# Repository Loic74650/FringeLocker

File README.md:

# FringeLocker
## Intro
 FringeLocker, as its name indicates, is an electronic system designed to lock interference fringes of an optical interferometer or a holography recording setup.
 The purpose of locking an interferometer is usually to stabilize unstable interference fringes due to mechanical vibrations or thermal drifts.<br />
 Demo video: https://youtu.be/0IrlpE1sPkQ
 
  <br />
  <br />
  <br />
  <br /><br />
 
## Working principle
Two photodiodes sample the interference fringes and detect any movement of those. 
A low noise amplifier and feedback loop drive a mirror which is placed on a piezo transducer in order to move one arm of the interferometer and compensate for the detected fringe movements

## Setup
This version of FringeLocker is powered by two MN21/A23 12V batteries. Alternatively connector J3 on the board can be used to power the board with an external supply of
your choice (remove the batteries first!). The board accepts supply voltages up to +/-18Volts and so currently I am using two 9V batteries in series for each voltage ramp in order to increase lifetime on battery.
The photodiodes need to be masked of, leaving just one slit 0.5mm wide per photodiode. See image in the photos folder.<br />
Slider switch SW2 switched ON/OFF the board.  
There are three adjustments to be performed on the board. 

1- Servo Gain
RV1 10 turns potentiometer adjusts the servo gain. Start by adjusting it to minimum

2- Output bias
RV2 10 turns potentiometer adjusts the level of bias voltage to the piezo transducer. Since positive or negative voltages can be applied to the transducer it is necessary to apply
a bias to it. Use a voltmeter to measure the bias voltage between ground (the pcb mounting holes in each corner are grounded) and Test Point 2 (TP2 or TP Bias) and adjust it to 18 volts or so.

3- PresScaler switch
SW1 is a rotary switch which selects a preamplification of the photodiodes signal with various gains. Start by adjusting it to minimum

## Servo loop adjustment
Place the photodiodes within interference fringes of the interferometer. Adjust the interference fringes spacing so that their spacing is approximately 15mm (twice the spacing between the photodiodes). 
Power the board and start with the lowest gain on the PreScaler switch SW1 and move to larger gains incrementally until the feedback loop starts oscillating.
Revert to the previous gain setting in order to stop the oscillation. You can then fine adjust the loop gain RV1 by increasing it slowly until the loop starts oscillating, then reverting a bit to stop the oscillation.

## Bugs
An unpolarized 100nF capacitor needs to be manually added in parallel with R2 in order to create an active low pass filter and prevent the feedback loop from oscillating

## Credits
Thanks to Phil Hobbs for his help on the schematic design

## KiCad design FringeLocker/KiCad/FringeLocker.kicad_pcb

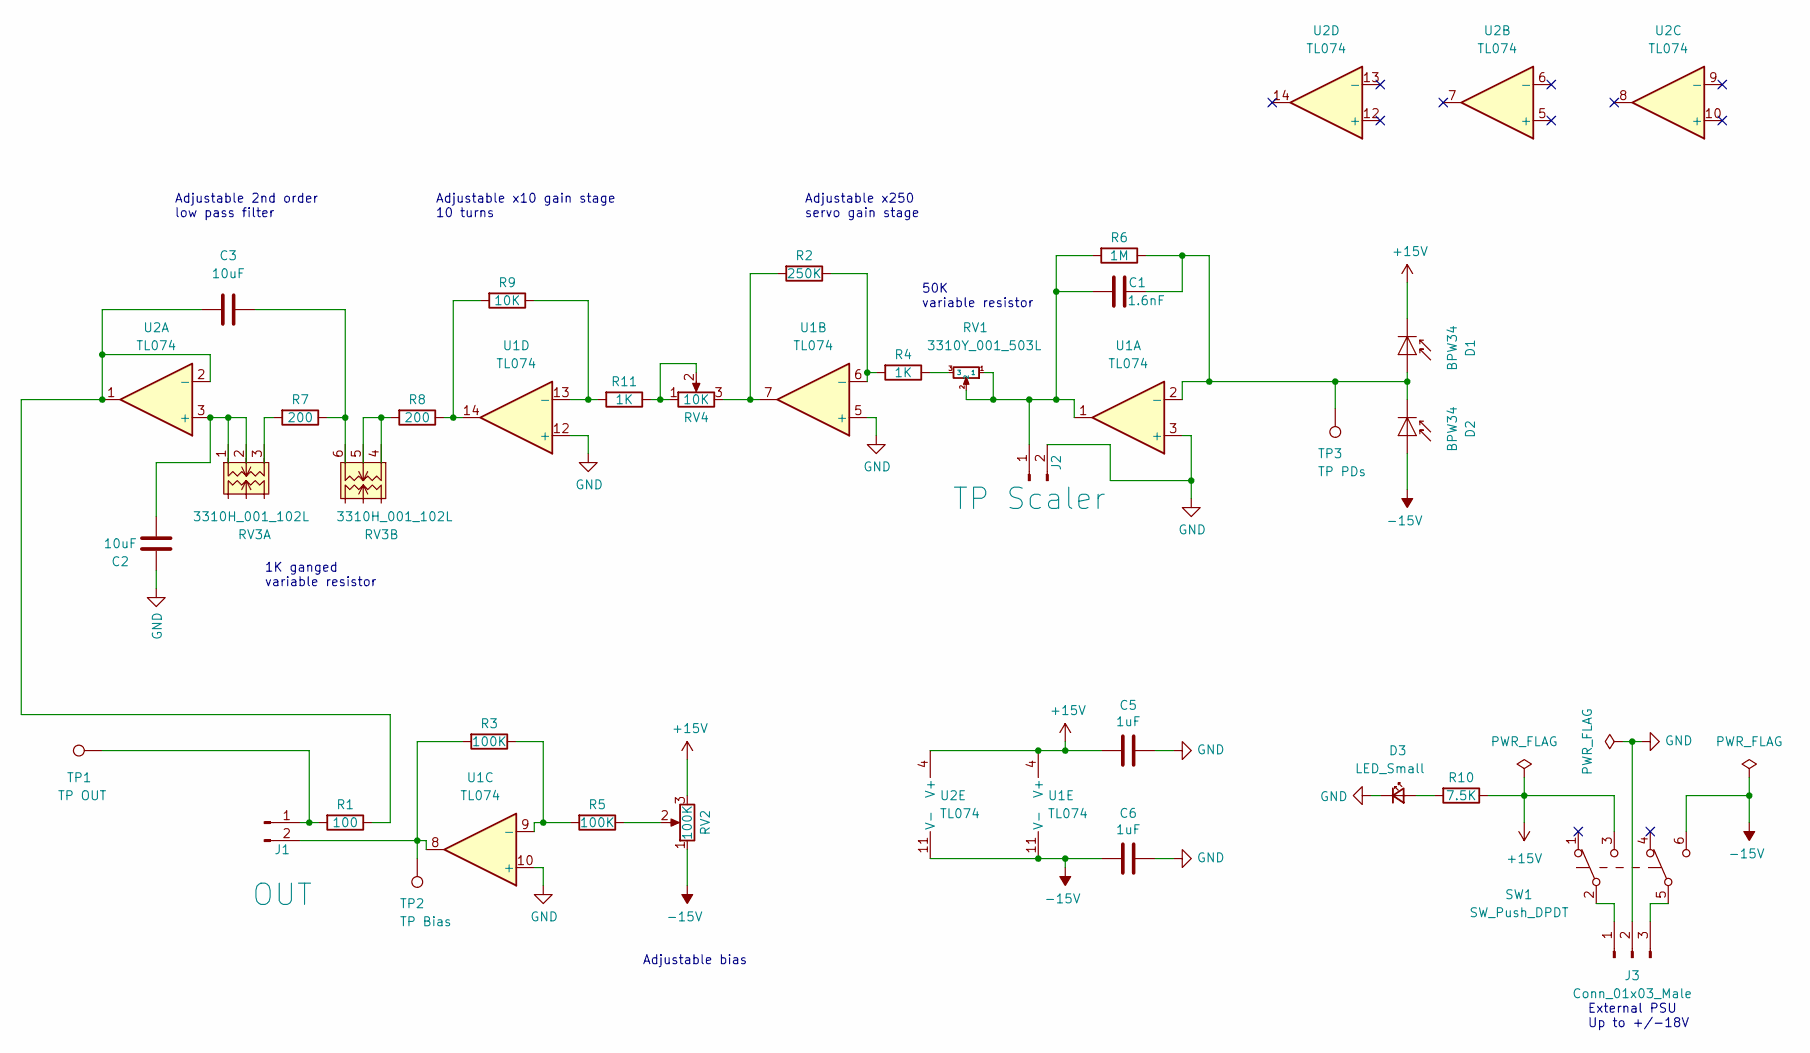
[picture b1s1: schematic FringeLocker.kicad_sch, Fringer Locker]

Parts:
C1: 1.6nF; C_0603_1608Metric_Pad1.08x0.95mm_HandSolder
C2, C3: 10uF; C_1210_3225Metric_Pad1.33x2.70mm_HandSolder
C5, C6: 1uF; C_0603_1608Metric_Pad1.08x0.95mm_HandSolder
D1, D2: BPW34; Osram_DIL2_4.3x4.65mm_P5.08mm
D3: LED_Small; LED_0805_2012Metric_Pad1.15x1.40mm_HandSolder
J1: OUT; PinHeader_1x02_P2.54mm_Vertical
J2: TP Scaler; PinHeader_1x02_P2.54mm_Vertical
J3: Conn_01x03_Male; PinHeader_1x03_P2.54mm_Vertical
R1: 100; R_0805_2012Metric_Pad1.20x1.40mm_HandSolder
R2: 250K; R_0805_2012Metric_Pad1.20x1.40mm_HandSolder
R3, R5: 100K; R_0805_2012Metric_Pad1.20x1.40mm_HandSolder
R4, R11: 1K; R_0805_2012Metric_Pad1.20x1.40mm_HandSolder
R6: 1M; R_0805_2012Metric_Pad1.20x1.40mm_HandSolder
R7, R8: 200; R_0805_2012Metric_Pad1.20x1.40mm_HandSolder
R9: 10K; R_0805_2012Metric_Pad1.20x1.40mm_HandSolder
R10: 7.5K; R_0805_2012Metric_Pad1.20x1.40mm_HandSolder
RV1: 3310Y_001_503L; Bourns3310Y
RV2: 100K; Potentiometer_Bourns_3266W_Vertical
RV3: 3310H_001_102L; Bourns3310H
RV4: 10K; Potentiometer_Bourns_3266W_Vertical
SW1: SW_Push_DPDT; SlideSwitchASE_DPDT
TP1: TP OUT; TestPoint_THTPad_D1.0mm_Drill0.5mm
TP2: TP Bias; TestPoint_THTPad_D1.0mm_Drill0.5mm
TP3: TP PDs; TestPoint_THTPad_D1.0mm_Drill0.5mm
U1, U2: TL074; SO-14_5.3x10.2mm_P1.27mm

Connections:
+15V: C5.1, D1.1 (K), R10.1, RV2.3, SW1.3 (C), U1.4 (V+), U2.4 (V+)
-15V: C6.1, D2.2 (A), RV2.1, SW1.6 (C), U1.11 (V-), U2.11 (V-)
GND: C2.2, C5.2, C6.2, D3.1 (K), J2.2, J3.2, U1.3 (+), U1.5 (+), U1.10 (+), U1.12 (+); also elsewhere on the board
unnamed: C1.1, J2.1, R6.2, RV1.1, RV1.2, U1.1
unnamed: C1.2, D1.2 (A), D2.1 (K), R6.1, TP3.1, U1.2 (-)
unnamed: C2.1, RV3.1 (A), RV3.2 (B), U2.3 (+)
unnamed: C3.1, R7.1, RV3.6 (F)
unnamed: C3.2, R1.1, U2.1, U2.2 (-)
unnamed: D3.2 (A), R10.2
unnamed: J1.1, R1.2, TP1.1
unnamed: J1.2, R3.2, TP2.1, U1.8
unnamed: J3.1, SW1.2 (B)
unnamed: J3.3, SW1.5 (B)
unnamed: R2.1, R4.2, U1.6 (-)
unnamed: R2.2, RV4.3, U1.7
unnamed: R3.1, R5.2, U1.9 (-)
unnamed: R4.1, RV1.3
unnamed: R5.1, RV2.2
unnamed: R7.2, RV3.3 (C)
unnamed: R8.1, R9.2, U1.14
unnamed: R8.2, RV3.4 (D), RV3.5 (E)
unnamed: R11.1, RV4.1, RV4.2
unnamed: R9.1, R11.2, U1.13 (-)

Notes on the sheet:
External PSU Up to +/-18V
Adjustable x10 gain stage 10 turns
Adjustable x250 servo gain stage
1K ganged variable resistor
Adjustable 2nd order low pass filter
50K variable resistor
Adjustable bias

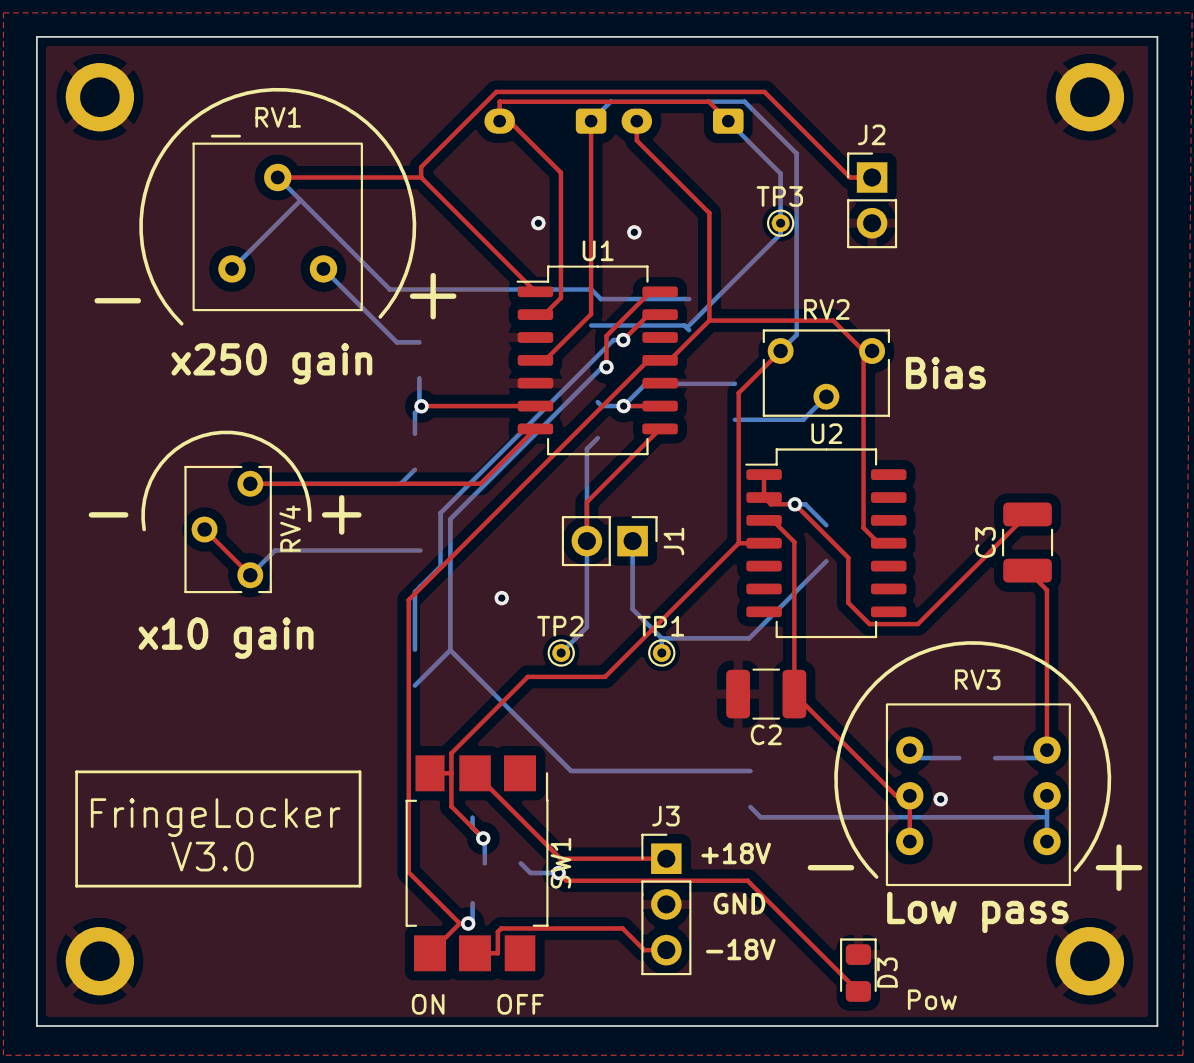
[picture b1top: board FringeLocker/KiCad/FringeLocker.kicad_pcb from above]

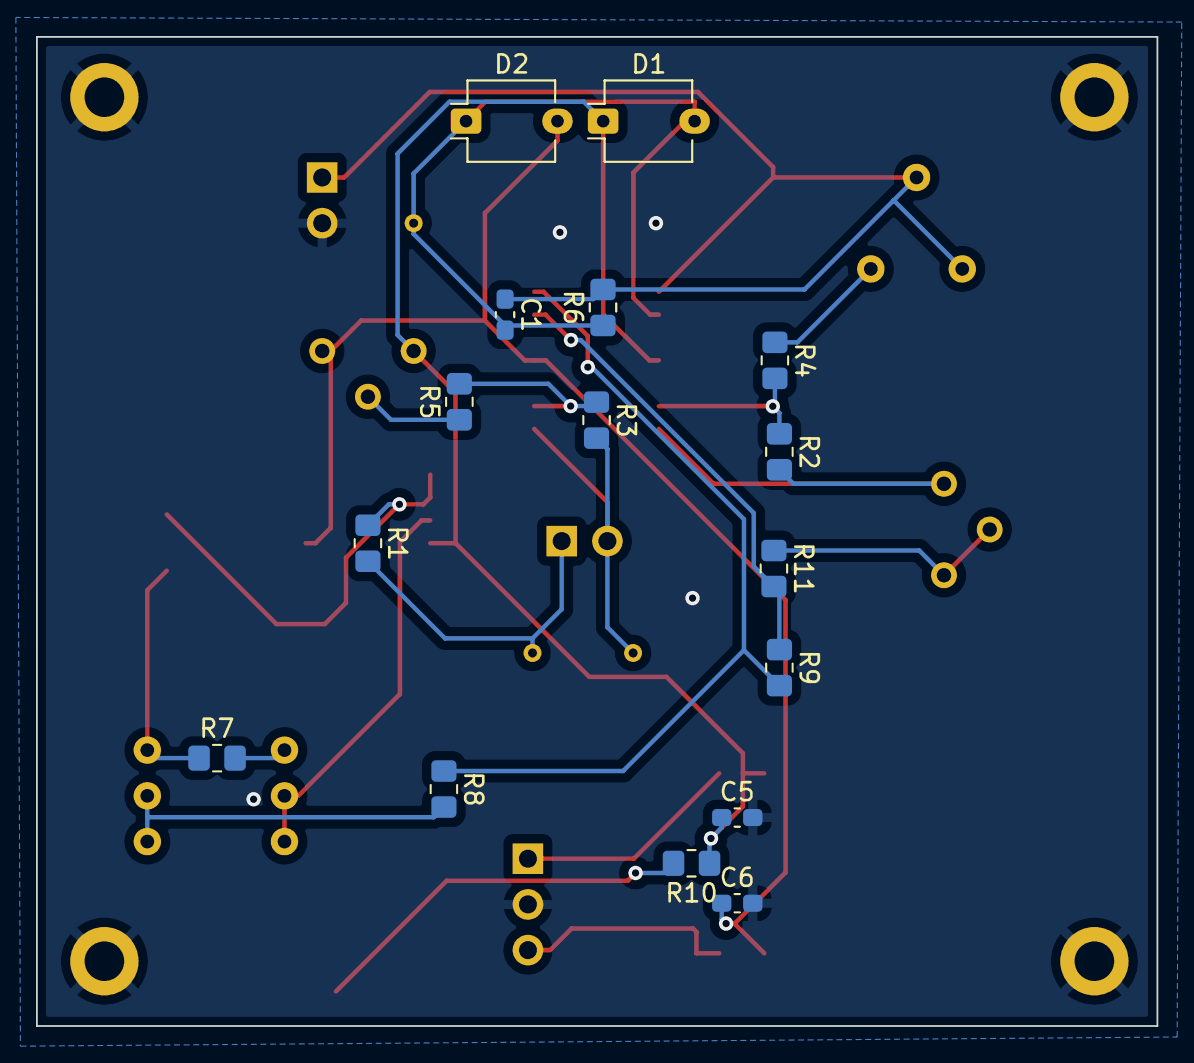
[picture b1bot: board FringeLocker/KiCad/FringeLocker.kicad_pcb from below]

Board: 2 copper layers, 62.2 x 54.9 mm, 36 parts (16 on the bottom side), 23 nets.

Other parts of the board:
REF1, REF2, REF3, REF4: MountingHole_2.2mm_M2_DIN965_Pad

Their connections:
GND: REF1.1, REF2.1, REF3.1, REF4.1; also elsewhere on the board

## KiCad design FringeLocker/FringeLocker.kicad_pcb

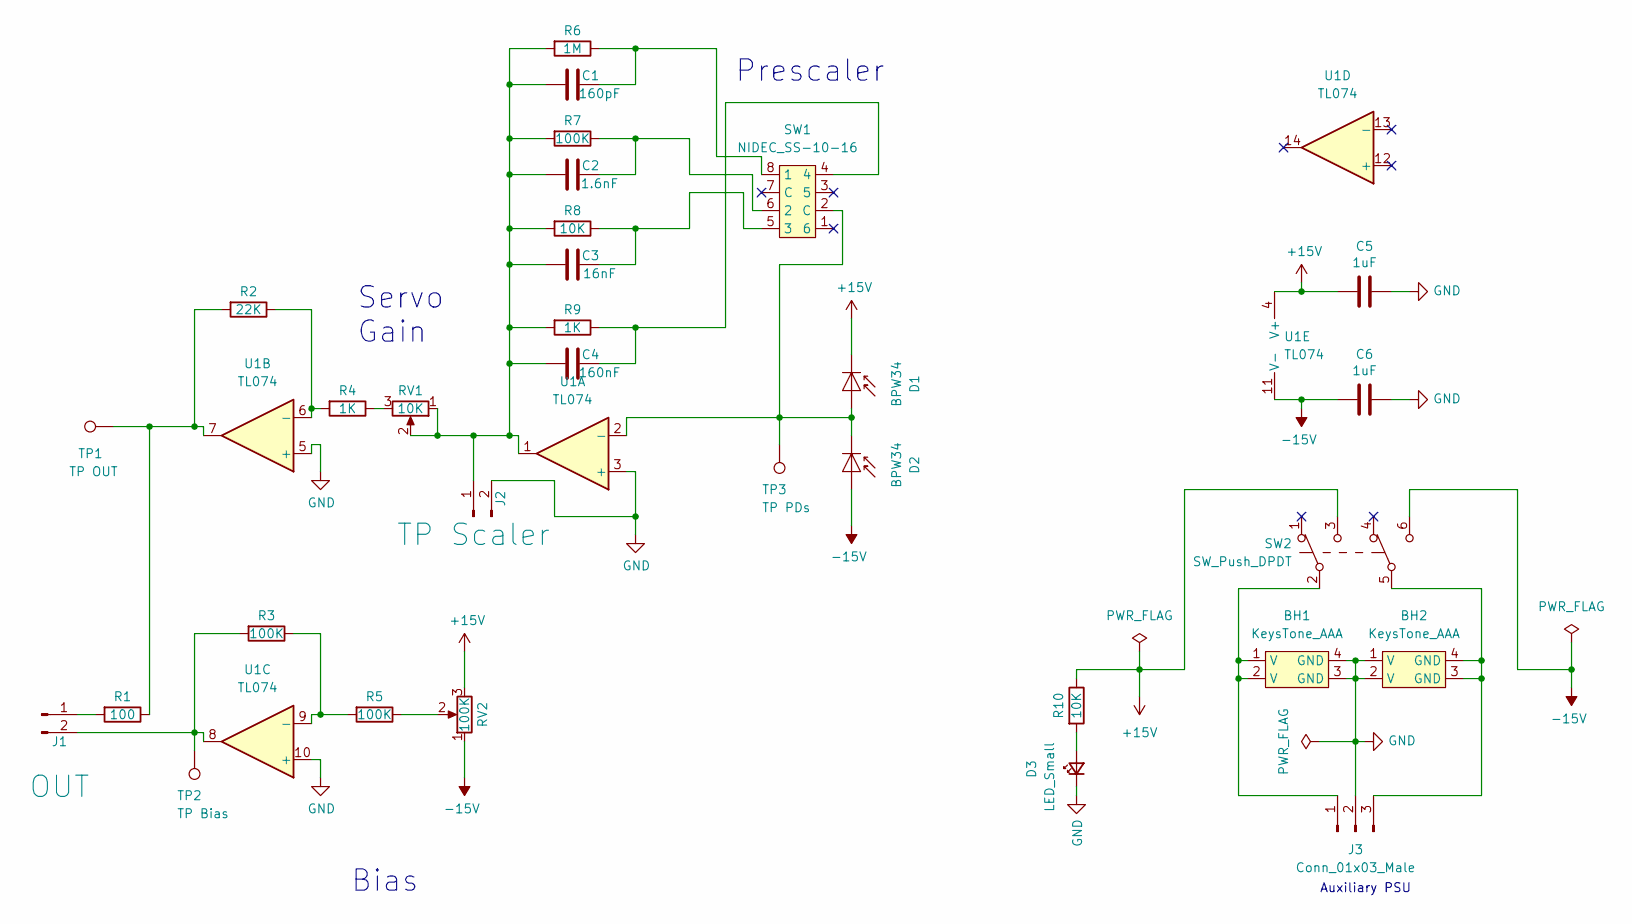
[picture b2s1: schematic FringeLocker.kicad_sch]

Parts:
BH1, BH2: KeysTone_AAA; Keystone_AAA
C1: 160pF; C_0603_1608Metric_Pad1.08x0.95mm_HandSolder
C2: 1.6nF; C_0603_1608Metric_Pad1.08x0.95mm_HandSolder
C3: 16nF; C_0603_1608Metric_Pad1.08x0.95mm_HandSolder
C4: 160nF; C_0603_1608Metric_Pad1.08x0.95mm_HandSolder
C5, C6: 1uF; C_0603_1608Metric_Pad1.08x0.95mm_HandSolder
D1, D2: BPW34; Osram_DIL2_4.3x4.65mm_P5.08mm
D3: LED_Small; LED_0402_1005Metric_Pad0.77x0.64mm_HandSolder
J1: OUT; PinHeader_1x02_P2.54mm_Vertical
J2: TP Scaler; PinHeader_1x02_P2.54mm_Vertical
J3: Conn_01x03_Male; PinHeader_1x03_P2.54mm_Vertical
R1: 100; R_0805_2012Metric_Pad1.20x1.40mm_HandSolder
R2: 22K; R_0805_2012Metric_Pad1.20x1.40mm_HandSolder
R3, R5, R7: 100K; R_0805_2012Metric_Pad1.20x1.40mm_HandSolder
R4, R9: 1K; R_0805_2012Metric_Pad1.20x1.40mm_HandSolder
R6: 1M; R_0805_2012Metric_Pad1.20x1.40mm_HandSolder
R8, R10: 10K; R_0805_2012Metric_Pad1.20x1.40mm_HandSolder
RV1: 10K; Potentiometer_Bourns_3266W_Vertical
RV2: 100K; Potentiometer_Bourns_3266W_Vertical
SW1: NIDEC_SS-10-16
SW2: SW_Push_DPDT; SlideSwitchASE_DPDT
TP1: TP OUT; TestPoint_THTPad_D1.0mm_Drill0.5mm
TP2: TP Bias; TestPoint_THTPad_D1.0mm_Drill0.5mm
TP3: TP PDs; TestPoint_THTPad_D1.0mm_Drill0.5mm
U1: TL074; SO-14_5.3x10.2mm_P1.27mm

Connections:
+15V: C5.1, D1.1 (K), R10.1, RV2.3, SW2.3 (C), U1.4 (V+)
-15V: C6.1, D2.2 (A), RV2.1, SW2.6 (C), U1.11 (V-)
GND: BH1.3 (GND), BH1.4 (GND), BH2.1 (V), BH2.2 (V), C5.2, C6.2, D3.1 (K), J2.2, J3.2, U1.3 (+), U1.5 (+), U1.10 (+); also elsewhere on the board
unnamed: BH1.1 (V), BH1.2 (V), J3.1, SW2.2 (B)
unnamed: BH2.3 (GND), BH2.4 (GND), J3.3, SW2.5 (B)
unnamed: C1.1, C2.1, C3.1, C4.1, J2.1, R6.2, R7.2, R8.2, R9.2, RV1.1, RV1.2, U1.1
unnamed: C1.2, R6.1, SW1.8 (1)
unnamed: C2.2, R7.1, SW1.6 (2)
unnamed: C3.2, R8.1, SW1.5 (3)
unnamed: C4.2, R9.1, SW1.4
unnamed: D1.2 (A), D2.1 (K), SW1.2 (C), TP3.1, U1.2 (-)
unnamed: D3.2 (A), R10.2
unnamed: J1.1, R1.2
unnamed: J1.2, R3.2, TP2.1, U1.8
unnamed: R1.1, R2.2, TP1.1, U1.7
unnamed: R2.1, R4.2, U1.6 (-)
unnamed: R3.1, R5.2, U1.9 (-)
unnamed: R4.1, RV1.3
unnamed: R5.1, RV2.2

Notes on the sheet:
Auxiliary PSU
Bias
Servo Gain
Prescaler

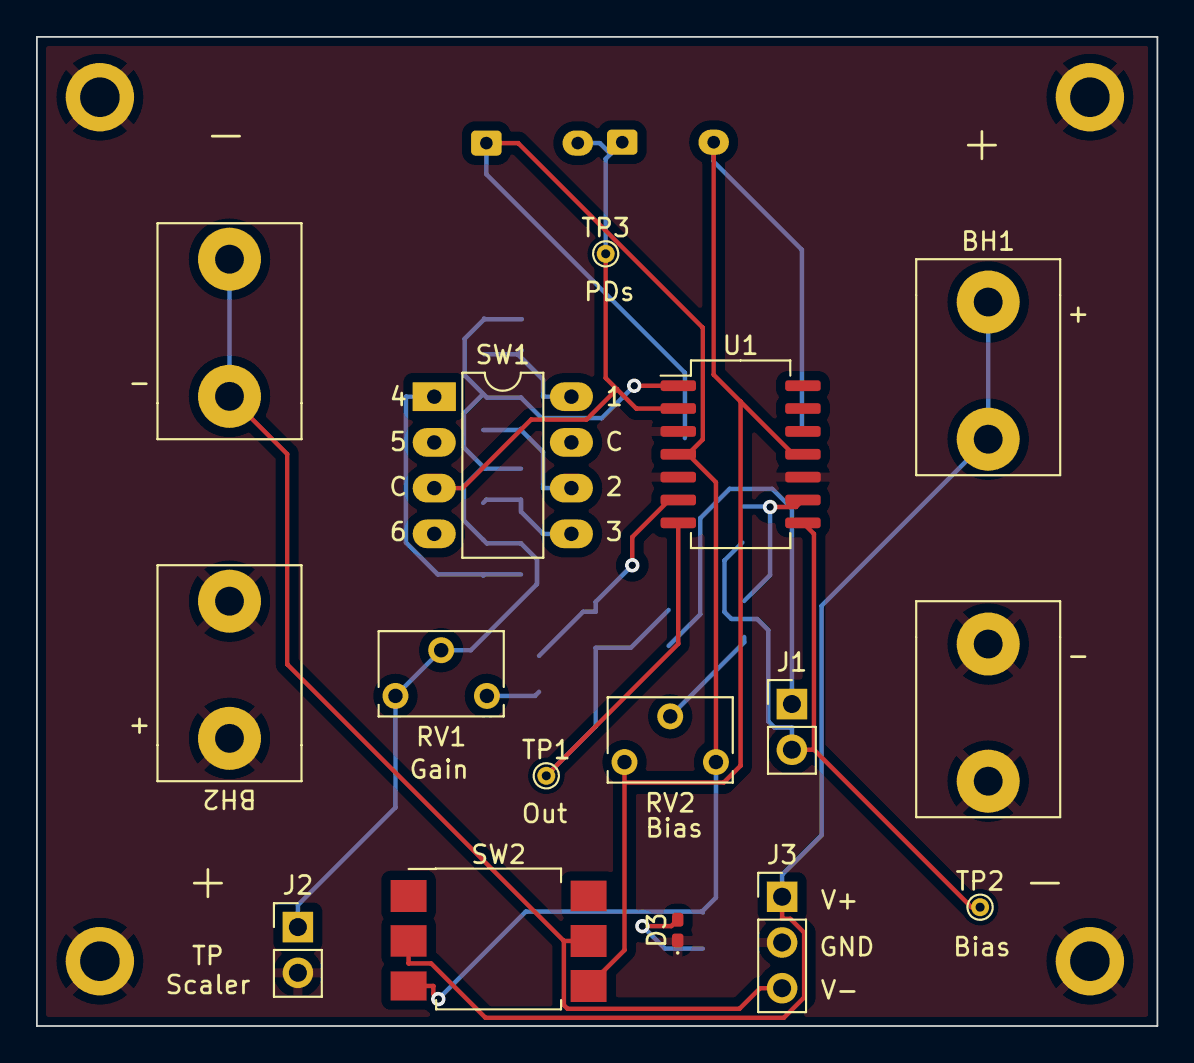
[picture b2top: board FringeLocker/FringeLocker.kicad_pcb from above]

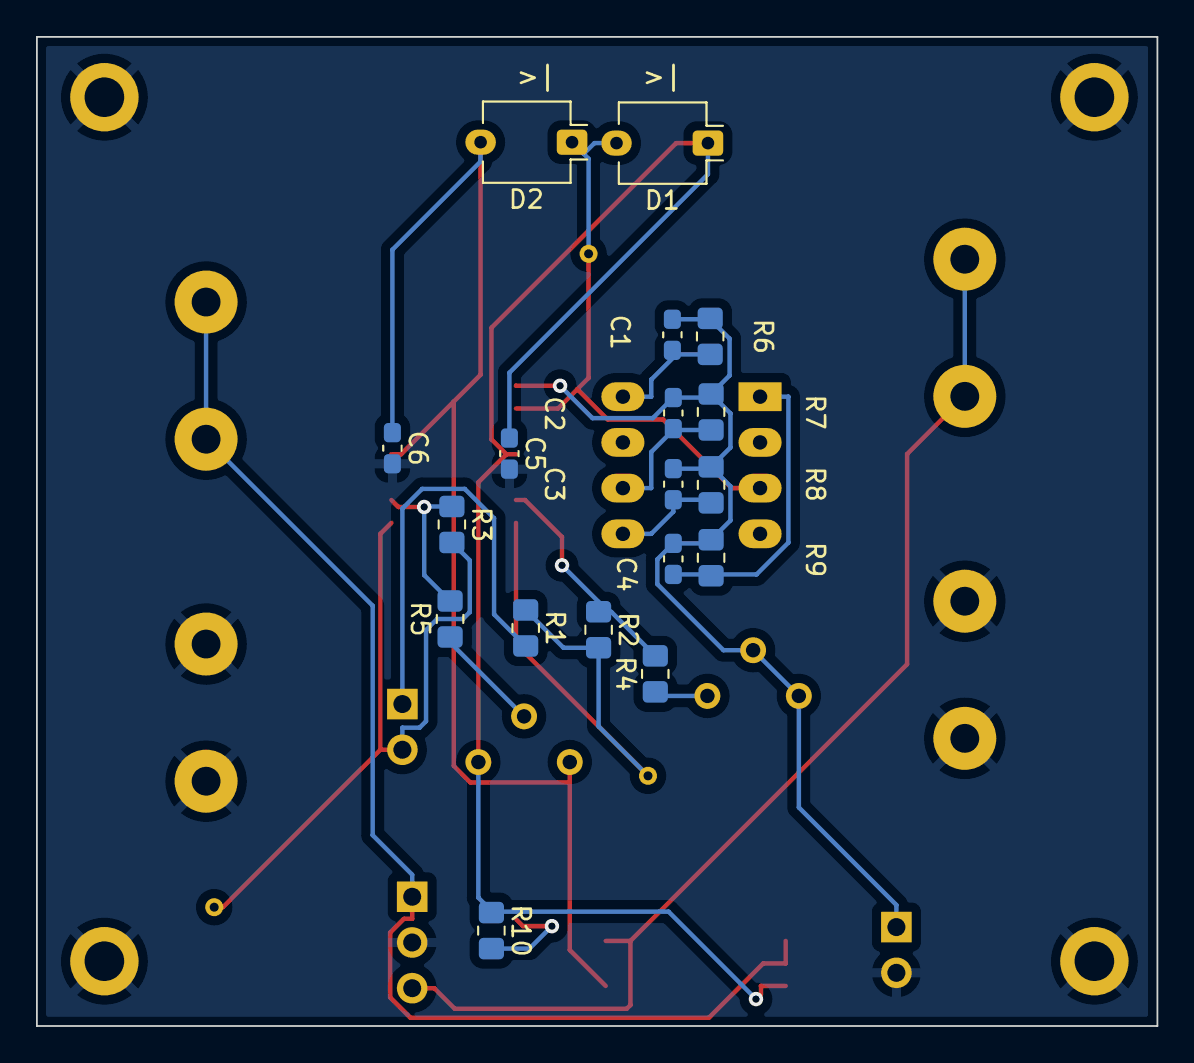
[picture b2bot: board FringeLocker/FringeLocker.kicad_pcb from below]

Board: 2 copper layers, 62.2 x 54.9 mm, 36 parts (18 on the bottom side), 19 nets.

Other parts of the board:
REF1, REF2, REF3, REF4: MountingHole_2.2mm_M2_DIN965_Pad

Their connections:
GND: REF1.1, REF2.2, REF3.3, REF4.4; also elsewhere on the board

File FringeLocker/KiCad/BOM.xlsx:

Column1 | Column2 | Column3 | Column4 | Column5 | Column6 | Column7 | Column8 | Column10
Source: | C:\Users\USER\Documents\GitHub\FringeLocker\FringeLocker\FringeLocker.kicad_sch
Date: | 15/02/2023 15:58:59
Tool: | Eeschema (6.0.11)
Generator: | C:\Program Files\KiCad\6.0\bin\scripting\plugins/bom_csv_grouped_by_value.py
Component Count: | 32
Individual Components:
Item | Qty | Reference(s) | Value | LibPart | Footprint | Datasheet | Unit price (€) | Total price (€)
 |  | BH1 | KeysTone_AAA | My_Library:KeysTone_AAA | BatteryHolder:Keystone_AAA
 |  | BH2 | KeysTone_AAA | My_Library:KeysTone_AAA | BatteryHolder:Keystone_AAA
 |  | C1 | 160pF | Device:C | Capacitor_SMD:C_0603_1608Metric_Pad1.08x0.95mm_HandSolder | ~
 |  | C2 | 1.6nF | Device:C | Capacitor_SMD:C_0603_1608Metric_Pad1.08x0.95mm_HandSolder | ~
 |  | C3 | 16nF | Device:C | Capacitor_SMD:C_0603_1608Metric_Pad1.08x0.95mm_HandSolder | ~
 |  | C4 | 160nF | Device:C | Capacitor_SMD:C_0603_1608Metric_Pad1.08x0.95mm_HandSolder | ~
 |  | C5 | 1uF | Device:C | Capacitor_SMD:C_0603_1608Metric_Pad1.08x0.95mm_HandSolder | ~
 |  | C6 | 1uF | Device:C | Capacitor_SMD:C_0603_1608Metric_Pad1.08x0.95mm_HandSolder | ~
 |  | D1 | BPW34 | Sensor_Optical:BPW34 | OptoDevice:Osram_DIL2_4.3x4.65mm_P5.08mm | http://www.vishay.com/docs/81521/bpw34.pdf
 |  | D2 | BPW34 | Sensor_Optical:BPW34 | OptoDevice:Osram_DIL2_4.3x4.65mm_P5.08mm | http://www.vishay.com/docs/81521/bpw34.pdf
 |  | D3 | LED_Small | Device:LED_Small | LED_SMD:LED_0402_1005Metric_Pad0.77x0.64mm_HandSolder | ~
 |  | J1 | OUT | Connector:Conn_01x02_Male | Connector_PinHeader_2.54mm:PinHeader_1x02_P2.54mm_Vertical | ~
 |  | J2 | TP Scaler | Connector:Conn_01x02_Male | Connector_PinHeader_2.54mm:PinHeader_1x02_P2.54mm_Vertical | ~
 |  | J3 | Conn_01x03_Male | Connector:Conn_01x03_Male | Connector_PinHeader_2.54mm:PinHeader_1x03_P2.54mm_Vertical | ~
 |  | R1 | 100 | Device:R | Resistor_SMD:R_0805_2012Metric_Pad1.20x1.40mm_HandSolder | ~
 |  | R2 | 22K | Device:R | Resistor_SMD:R_0805_2012Metric_Pad1.20x1.40mm_HandSolder | ~
 |  | R3 | 100K | Device:R | Resistor_SMD:R_0805_2012Metric_Pad1.20x1.40mm_HandSolder | ~
 |  | R4 | 1K | Device:R | Resistor_SMD:R_0805_2012Metric_Pad1.20x1.40mm_HandSolder | ~
 |  | R5 | 100K | Device:R | Resistor_SMD:R_0805_2012Metric_Pad1.20x1.40mm_HandSolder | ~
 |  | R6 | 1M | Device:R | Resistor_SMD:R_0805_2012Metric_Pad1.20x1.40mm_HandSolder | ~
 |  | R7 | 100K | Device:R | Resistor_SMD:R_0805_2012Metric_Pad1.20x1.40mm_HandSolder | ~
 |  | R8 | 10K | Device:R | Resistor_SMD:R_0805_2012Metric_Pad1.20x1.40mm_HandSolder | ~
 |  | R9 | 1K | Device:R | Resistor_SMD:R_0805_2012Metric_Pad1.20x1.40mm_HandSolder | ~
 |  | R10 | 10K | Device:R | Resistor_SMD:R_0805_2012Metric_Pad1.20x1.40mm_HandSolder | ~
 |  | RV1 | 10K | FringeLocker-rescue:R_POT-Device | Potentiometer_THT:Potentiometer_Bourns_3266W_Vertical
 |  | RV2 | 100K | FringeLocker-rescue:R_POT-Device | Potentiometer_THT:Potentiometer_Bourns_3266W_Vertical
 |  | SW1 | NIDEC_SS-10-16 | My_Library:NIDEC_SS-10-16 | BatteryHolder:NIDEC_SS-10-16
 |  | SW2 | SW_Push_DPDT | Switch:SW_Push_DPDT | BatteryHolder:SlideSwitchASE_DPDT | ~
 |  | TP1 | TP OUT | Connector:TestPoint | TestPoint:TestPoint_THTPad_D1.0mm_Drill0.5mm | ~
 |  | TP2 | TP Bias | Connector:TestPoint | TestPoint:TestPoint_THTPad_D1.0mm_Drill0.5mm | ~
 |  | TP3 | TP PDs | Connector:TestPoint | TestPoint:TestPoint_THTPad_D1.0mm_Drill0.5mm | ~
 |  | U1 | TL074 | Amplifier_Operational:TL074 | Package_SO:SO-14_5.3x10.2mm_P1.27mm | http://www.ti.com/lit/ds/symlink/tl071.pdf
Collated Components:
Item | Qty | Reference(s) | Value | LibPart | Footprint | Datasheet | Unit price (€) | Total price (€)
1 | 2 | BH1, BH2 | KeysTone_AAA | My_Library:KeysTone_AAA | BatteryHolder:Keystone_AAA |  | 0.38 | 0.76
2 | 1 | C1 | 160pF | Device:C | Capacitor_SMD:C_0603_1608Metric_Pad1.08x0.95mm_HandSolder | ~ | 0.1 | 0.1
3 | 1 | C2 | 1.6nF | Device:C | Capacitor_SMD:C_0603_1608Metric_Pad1.08x0.95mm_HandSolder | ~ | 0.1 | 0.1
4 | 1 | C3 | 16nF | Device:C | Capacitor_SMD:C_0603_1608Metric_Pad1.08x0.95mm_HandSolder | ~ | 0.1 | 0.1
5 | 1 | C4 | 160nF | Device:C | Capacitor_SMD:C_0603_1608Metric_Pad1.08x0.95mm_HandSolder | ~ | 0.1 | 0.1
6 | 2 | C5, C6 | 1uF | Device:C | Capacitor_SMD:C_0603_1608Metric_Pad1.08x0.95mm_HandSolder | ~ | 0.1 | 0.2
7 | 2 | D1, D2 | BPW34 | Sensor_Optical:BPW34 | OptoDevice:Osram_DIL2_4.3x4.65mm_P5.08mm | http://www.vishay.com/docs/81521/bpw34.pdf | 0.68 | 1.36
8 | 1 | D3 | LED_Small | Device:LED_Small | LED_SMD:LED_0402_1005Metric_Pad0.77x0.64mm_HandSolder | ~ | 0.43 | 0.43
9 | 1 | J1 | OUT | Connector:Conn_01x02_Male | Connector_PinHeader_2.54mm:PinHeader_1x02_P2.54mm_Vertical | ~ | 0.1 | 0.1
10 | 1 | J2 | TP Scaler | Connector:Conn_01x02_Male | Connector_PinHeader_2.54mm:PinHeader_1x02_P2.54mm_Vertical | ~ | 0.1 | 0.1
11 | 1 | J3 | Conn_01x03_Male | Connector:Conn_01x03_Male | Connector_PinHeader_2.54mm:PinHeader_1x03_P2.54mm_Vertical | ~ | 0.1 | 0.1
12 | 1 | R1 | 100 | Device:R | Resistor_SMD:R_0805_2012Metric_Pad1.20x1.40mm_HandSolder | ~ | 0.1 | 0.1
13 | 1 | R2 | 22K | Device:R | Resistor_SMD:R_0805_2012Metric_Pad1.20x1.40mm_HandSolder | ~ | 0.1 | 0.1
14 | 3 | R3, R5, R7 | 100K | Device:R | Resistor_SMD:R_0805_2012Metric_Pad1.20x1.40mm_HandSolder | ~ | 0.1 | 0.30000000000000004
15 | 2 | R4, R9 | 1K | Device:R | Resistor_SMD:R_0805_2012Metric_Pad1.20x1.40mm_HandSolder | ~ | 0.1 | 0.2
16 | 1 | R6 | 1M | Device:R | Resistor_SMD:R_0805_2012Metric_Pad1.20x1.40mm_HandSolder | ~ | 0.1 | 0.1
17 | 2 | R8, R10 | 10K | Device:R | Resistor_SMD:R_0805_2012Metric_Pad1.20x1.40mm_HandSolder | ~ | 0.1 | 0.2
18 | 1 | RV1 | 10K | FringeLocker-rescue:R_POT-Device | Potentiometer_THT:Potentiometer_Bourns_3266W_Vertical |  | 2.4900000000000002 | 2.4900000000000002
19 | 1 | RV2 | 100K | FringeLocker-rescue:R_POT-Device | Potentiometer_THT:Potentiometer_Bourns_3266W_Vertical |  | 4.1900000000000004 | 4.1900000000000004
20 | 1 | SW1 | NIDEC_SS-10-16 | My_Library:NIDEC_SS-10-16 | BatteryHolder:NIDEC_SS-10-16 |  | 3.88 | 3.88
21 | 1 | SW2 | SW_Push_DPDT | Switch:SW_Push_DPDT | BatteryHolder:SlideSwitchASE_DPDT | ~ | 5.03 | 5.03
22 | 1 | TP1 | TP OUT | Connector:TestPoint | TestPoint:TestPoint_THTPad_D1.0mm_Drill0.5mm | ~ | 0 | 0
23 | 1 | TP2 | TP Bias | Connector:TestPoint | TestPoint:TestPoint_THTPad_D1.0mm_Drill0.5mm | ~ | 0 | 0
24 | 1 | TP3 | TP PDs | Connector:TestPoint | TestPoint:TestPoint_THTPad_D1.0mm_Drill0.5mm | ~ | 0 | 0
25 | 1 | U1 | TL074 | Amplifier_Operational:TL074 | Package_SO:SO-14_5.3x10.2mm_P1.27mm | http://www.ti.com/lit/ds/symlink/tl071.pdf | 0.84 | 0.84
 |  |  |  |  |  |  |  | 0
 |  |  |  |  |  |  |  | 0
 |  |  |  |  |  |  |  | 0
 | 1 | PCB |  | JLCPCB |  | JLPCB | 5 | 5
 |  |  |  |  |  |  | TOTAL | 25.880000000000003

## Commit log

2023-02-10 started PCB
2023-02-12 Added 23A PSU
2023-02-15 V1.0
2023-02-15 V1.0 docs and 3D files
2023-02-16 Added PiezoDisc 3D supports
2023-02-16 Reorg of folders
2023-03-24 V2.0
2023-03-25 Added photos
2023-04-19 V3.0
    Added a x10 gain stage and a 2nd order adjustable low pass filter
    Removed battery holders, requires external +/-15V to +/-18V supply

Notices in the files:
FringeLocker/KiCad/FringeLocker.kicad_sch:
©Loic74650
